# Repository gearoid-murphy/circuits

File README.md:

# circuits
Repo for Kicad / FlatCam / CNC workflows

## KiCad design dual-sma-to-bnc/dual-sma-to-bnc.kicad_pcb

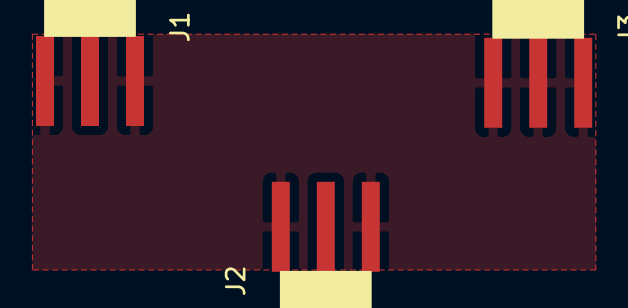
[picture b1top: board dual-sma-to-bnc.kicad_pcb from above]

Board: 2 copper layers, 3 parts (0 on the bottom side), 2 nets, no tracks yet.

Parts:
J1, J2, J3: Conn_Coaxial; amazon-sma-connector

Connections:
GND: J1.2, J2.2, J3.1, J3.2
unnamed: J1.1, J2.1

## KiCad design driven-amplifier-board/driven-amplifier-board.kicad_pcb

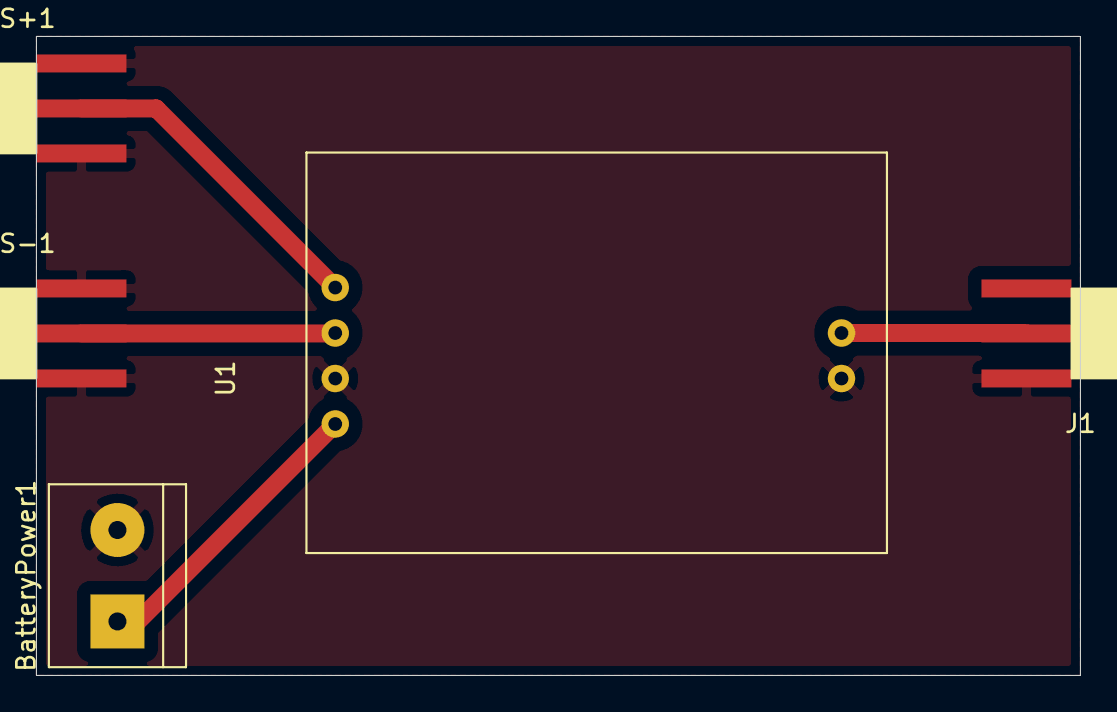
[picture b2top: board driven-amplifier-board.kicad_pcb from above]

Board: 2 copper layers, 58.0 x 35.5 mm, 5 parts (0 on the bottom side), 5 nets.

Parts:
BatteryPower1: Screw_Terminal_01x02; TerminalBlock_bornier-2_P5.08mm
J1: Conn_Coaxial; amazon-sma-connector
S+1: Conn_Coaxial; amazon-sma-connector
S-1: Conn_Coaxial; amazon-sma-connector
U1: Teyleten-Differential-Amplifier

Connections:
GND: BatteryPower1.2, J1.2, S+1.2, S-1.2, U1.3, U1.6
unnamed: BatteryPower1.1, U1.4
unnamed: J1.1, U1.5
unnamed: S+1.1, U1.1
unnamed: S-1.1, U1.2

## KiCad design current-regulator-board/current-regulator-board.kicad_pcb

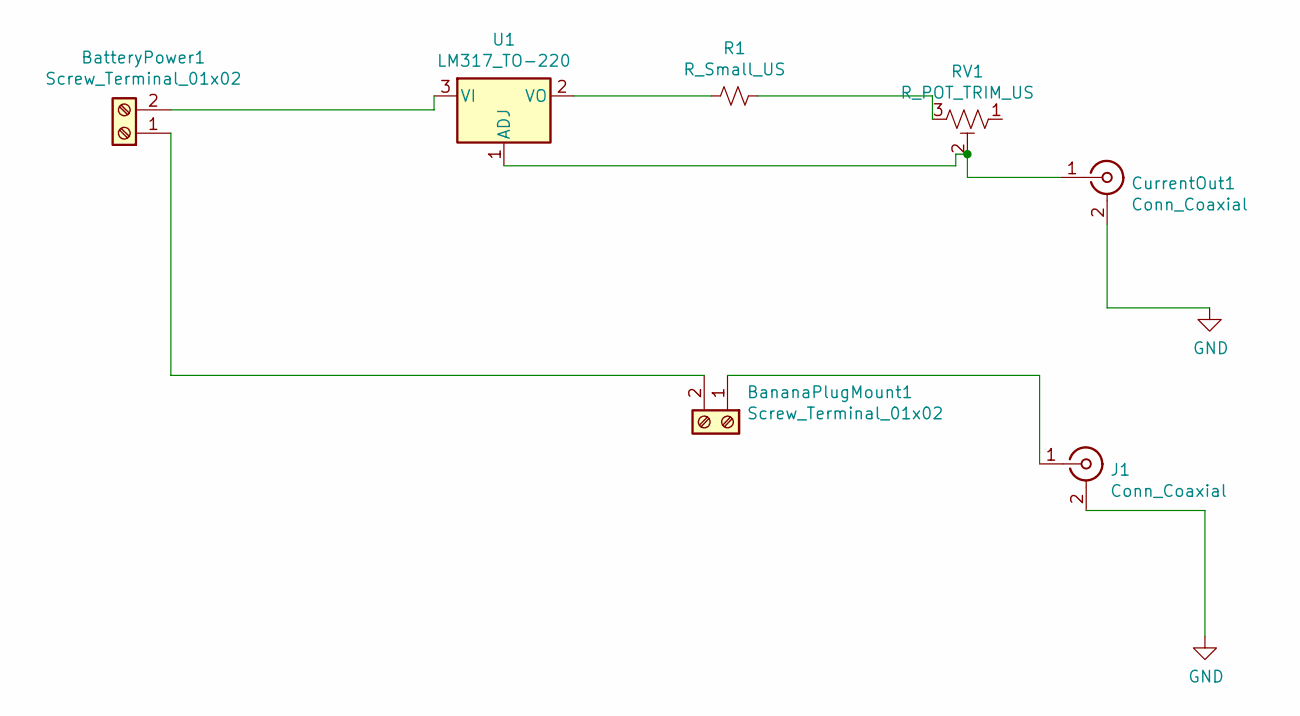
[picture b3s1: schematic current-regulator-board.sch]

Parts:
BananaPlugMount1: Screw_Terminal_01x02; Amazon_Banana_Jack_2Pin
BatteryPower1: Screw_Terminal_01x02; TerminalBlock_bornier-2_P5.08mm
CurrentOut1: Conn_Coaxial; amazon-sma-connector
J1: Conn_Coaxial; amazon-sma-connector
R1: R_Small_US; R_Axial_DIN0207_L6.3mm_D2.5mm_P10.16mm_Horizontal
RV1: R_POT_TRIM_US; Potentiometer_Bourns_3266Z_Horizontal
U1: LM317_TO-220; TO-220-3_Vertical

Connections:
GND: CurrentOut1.2 (Ext), J1.2 (Ext)
unnamed: BananaPlugMount1.1, J1.1 (In)
unnamed: BananaPlugMount1.2, BatteryPower1.1
unnamed: BatteryPower1.2, U1.3 (VI)
unnamed: CurrentOut1.1 (In), RV1.2, U1.1 (ADJ)
unnamed: R1.1, RV1.3
unnamed: R1.2, U1.2 (VO)

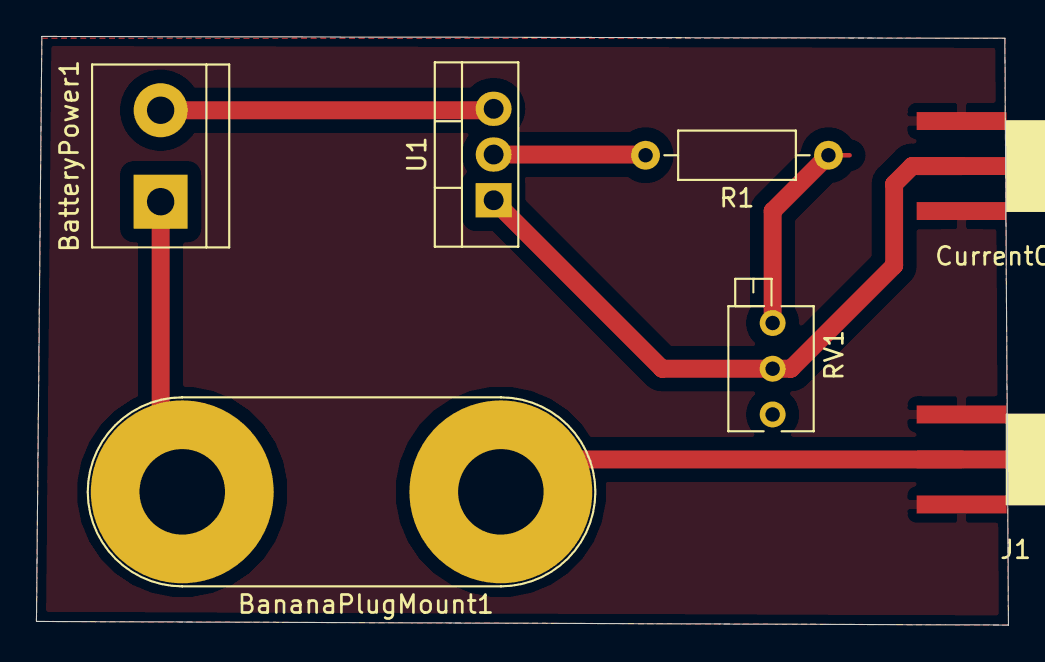
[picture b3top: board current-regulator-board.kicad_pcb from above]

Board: 2 copper layers, 54.0 x 32.7 mm, 7 parts (0 on the bottom side), 7 nets.

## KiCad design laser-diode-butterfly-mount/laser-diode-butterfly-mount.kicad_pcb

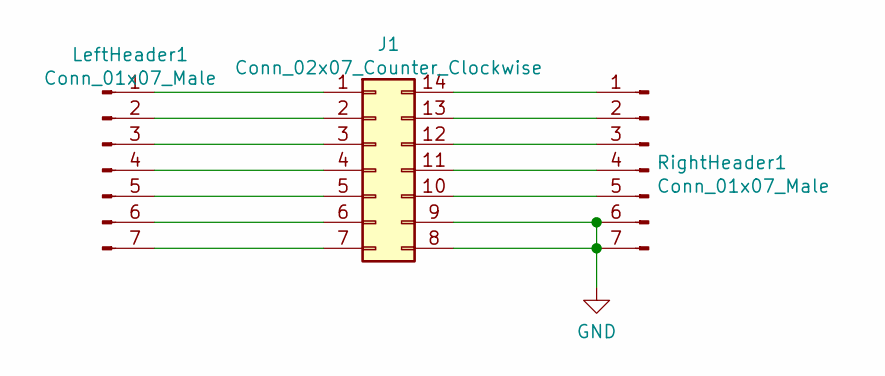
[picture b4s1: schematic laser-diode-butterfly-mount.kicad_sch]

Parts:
J1: Conn_02x07_Counter_Clockwise; laser-diode-butterfly-mount
LeftHeader1: Conn_01x07_Male; PinSocket_1x07_P2.54mm_Vertical
RightHeader1: Conn_01x07_Male; PinSocket_1x07_P2.54mm_Vertical

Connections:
GND: J1.8, J1.9, RightHeader1.6, RightHeader1.7
unnamed: J1.1, LeftHeader1.1
unnamed: J1.2, LeftHeader1.2
unnamed: J1.3, LeftHeader1.3
unnamed: J1.4, LeftHeader1.4
unnamed: J1.5, LeftHeader1.5
unnamed: J1.6, LeftHeader1.6
unnamed: J1.7, LeftHeader1.7
unnamed: J1.10, RightHeader1.5
unnamed: J1.11, RightHeader1.4
unnamed: J1.12, RightHeader1.3
unnamed: J1.13, RightHeader1.2
unnamed: J1.14, RightHeader1.1

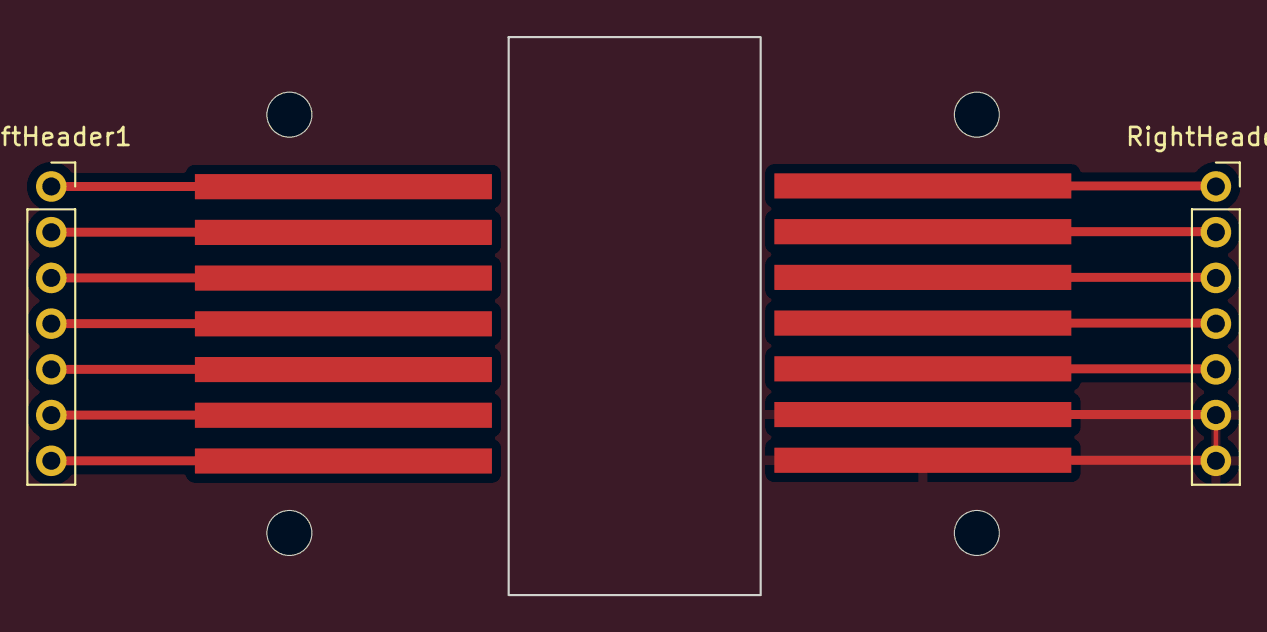
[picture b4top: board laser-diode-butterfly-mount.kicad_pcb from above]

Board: 2 copper layers, 14.0 x 31.0 mm, 3 parts (0 on the bottom side), 13 nets.

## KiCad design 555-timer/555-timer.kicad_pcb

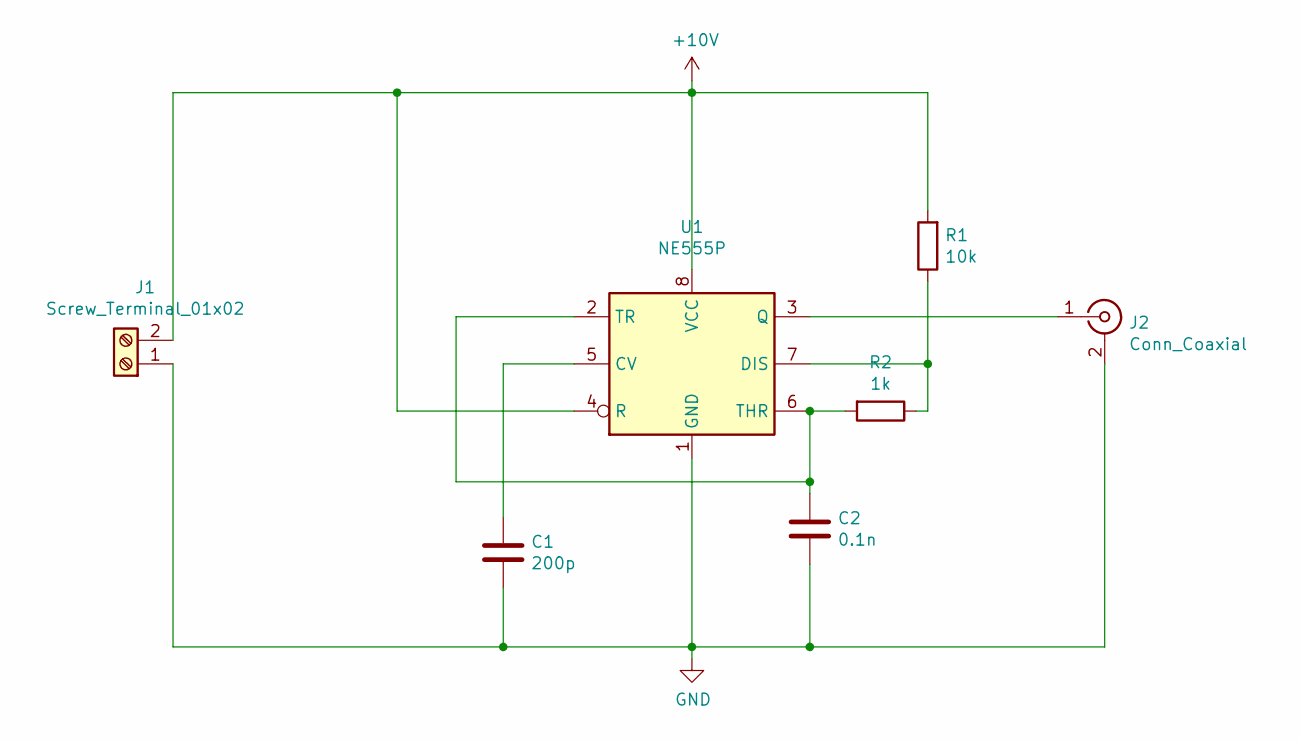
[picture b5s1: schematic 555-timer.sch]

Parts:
C1: 200p; CP_Radial_D8.0mm_P5.00mm
C2: 0.1n; CP_Radial_D8.0mm_P5.00mm
J1: Screw_Terminal_01x02; 2-port_banana_plug_block
J2: Conn_Coaxial; SMA_Amphenol_132289_EdgeMount
R1: 10k; R_Axial_DIN0207_L6.3mm_D2.5mm_P7.62mm_Horizontal
R2: 1k; R_Axial_DIN0207_L6.3mm_D2.5mm_P7.62mm_Horizontal
U1: NE555P; DIP-8_W7.62mm_Socket

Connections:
+10V: J1.2, R1.2, U1.4 (R), U1.8 (VCC)
GND: C1.2, C2.2, J1.1, J2.2 (Ext), U1.1 (GND)
unnamed: C1.1, U1.5 (CV)
unnamed: C2.1, R2.2, U1.2 (TR), U1.6 (THR)
unnamed: J2.1 (In), U1.3 (Q)
unnamed: R1.1, R2.1, U1.7 (DIS)

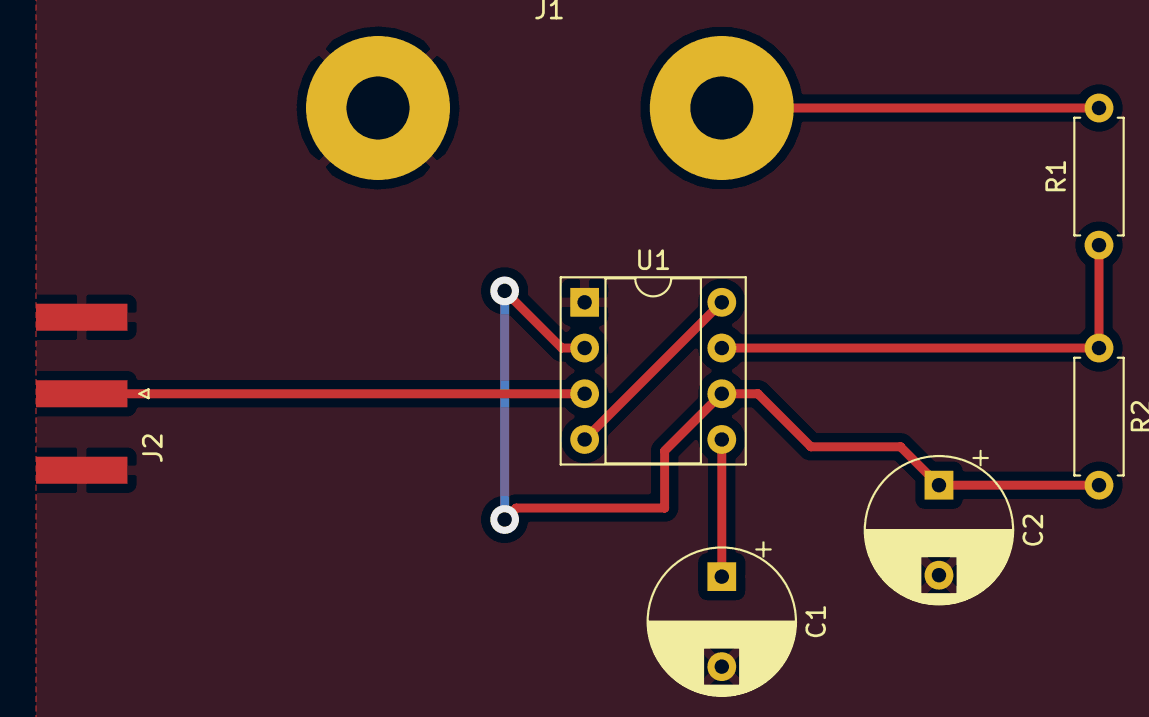
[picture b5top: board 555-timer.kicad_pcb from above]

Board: 2 copper layers, 7 parts (0 on the bottom side), 6 nets.

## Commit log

2022-04-02 Adding the first batch of projects.
2022-04-03 Added more projects.
2022-04-07 PCB layout refactoring.
2022-04-09 Added v0 amplifier board.
2022-04-09 Probe updates. Also suppressed gbr and drl files in git.
2022-04-12 Added the current regulator board.
2022-04-30 Updates.
2022-07-26 Updated the probe layout.
2022-07-28 Saving some old modifications.
2022-09-07 Local mods.
